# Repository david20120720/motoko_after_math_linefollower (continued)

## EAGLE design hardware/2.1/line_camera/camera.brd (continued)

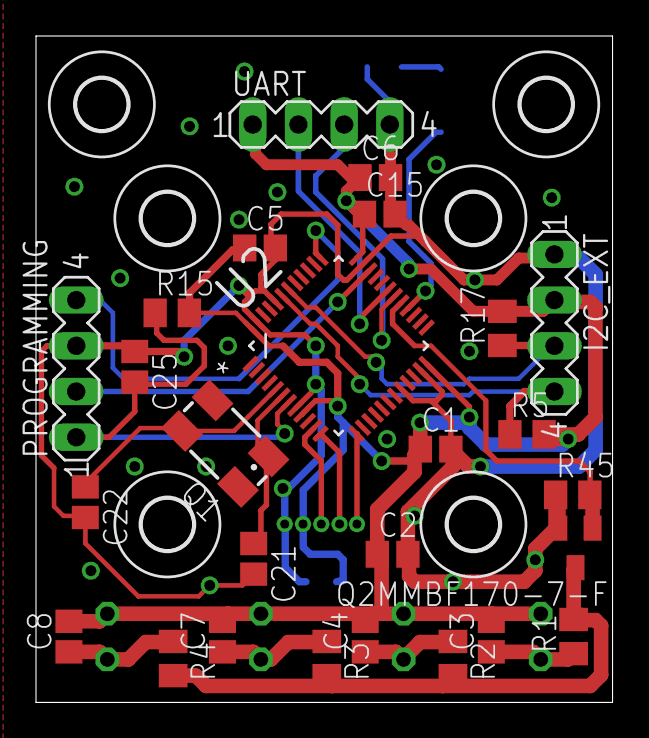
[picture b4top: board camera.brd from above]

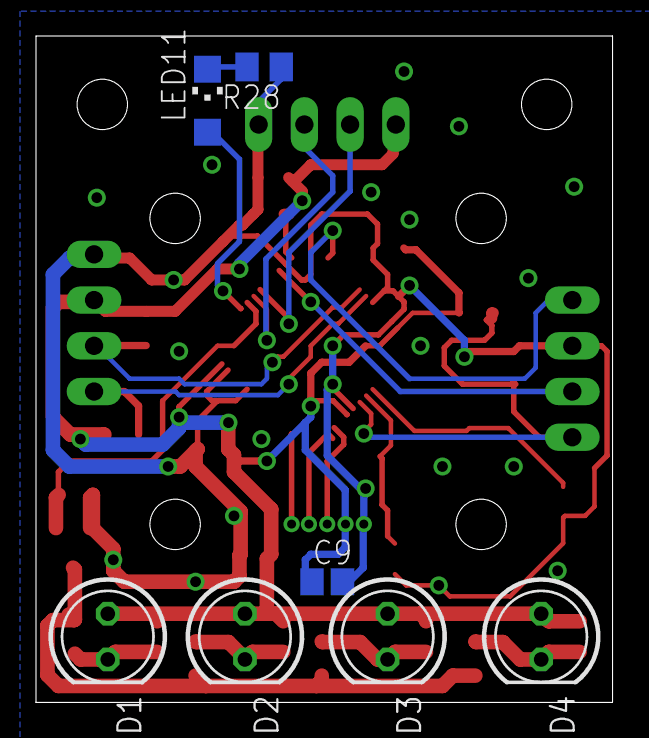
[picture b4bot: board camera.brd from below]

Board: 2 copper layers, 32.0 x 37.0 mm, 39 parts (7 on the bottom side), 19 nets.

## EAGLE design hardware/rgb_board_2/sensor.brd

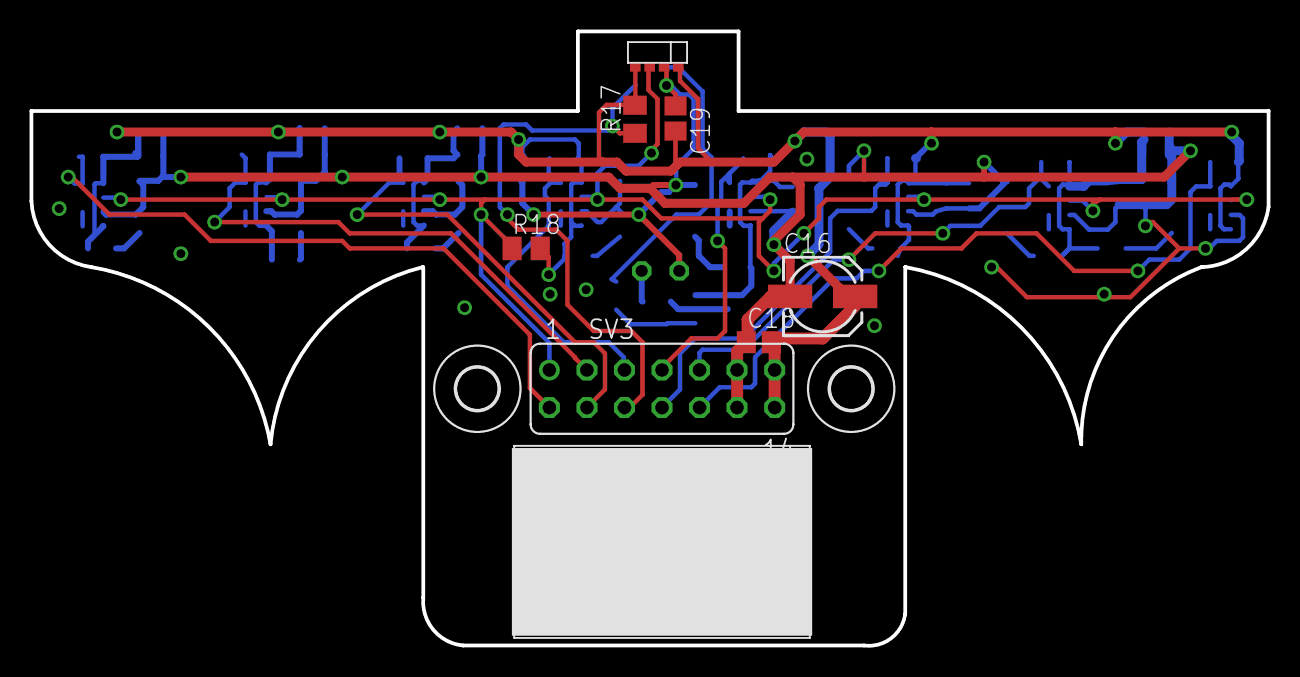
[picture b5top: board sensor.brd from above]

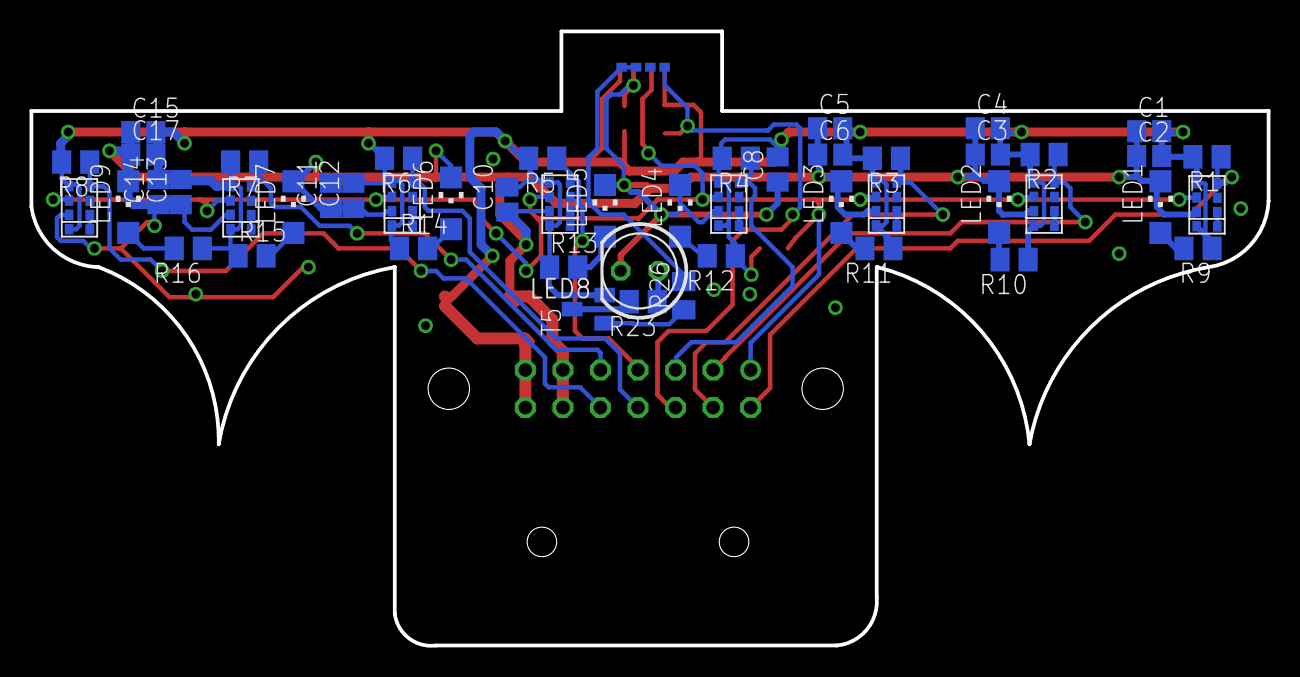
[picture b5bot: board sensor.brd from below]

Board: 2 copper layers, 83.7 x 41.6 mm, 60 parts (50 on the bottom side), 32 nets.

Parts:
C1, C3, C5, C11, C13, C15, C18: 10uF; C0805
C2, C4, C6, C8, C10, C12, C14, C17, C19: 100n; C0805
C16: 22uF; 153CLV-0505
H3, H4: MOUNT-HOLE2.8; 2,8
LED1, LED2, LED3, LED4, LED5, LED6, LED7, LED9: CHIPLED_1206
LED8: LED5MM
R1, R2, R3, R4, R5, R6, R7, R8, R17, R18: 4k7; M0805
R9, R10, R11, R12, R13, R14, R15, R16, R26: 330; M0805
R23: 22; M0805
SV3: FE07-2
T5: SOT23-BEC
U$1, U$4, U$5, U$6, U$7, U$8, U$9, U$10: APDS9950
U$2: APDS9950_EDGE
U$3: BALL_HOLE

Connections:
+3V3: C1.2, C2.2, C3.2, C4.2, C5.2, C6.2, C8.2, C10.2, C11.2, C12.2, C13.2, C14.2, C15.2, C16.+, C17.2, C18.2, C19.2, R1.2, R2.2, R3.2, R4.2, R5.2, R6.2, R7.2, R8.2, R9.1, R10.1, R11.1, R12.1, R13.1, R14.1, R15.1, R16.1, R17.2, R18.2, SV3.13, SV3.14, T5.E, U$1.P$5, U$1.P$8, U$2.P$5, U$2.P$8, U$4.P$5, U$4.P$8, U$5.P$5, U$5.P$8, U$6.P$5, U$6.P$8, U$7.P$5, U$7.P$8, U$8.P$5, U$8.P$8, U$9.P$5, U$9.P$8, U$10.P$5, U$10.P$8
ADC0_: R8.1, SV3.10, U$10.P$1
ADC1_: R7.1, SV3.9, U$9.P$1
ADC2_: R6.1, SV3.8, U$8.P$1
ADC3_: R5.1, SV3.7, U$7.P$1
ADC4_: R4.1, SV3.5, U$6.P$1
ADC5_: R3.1, SV3.4, U$5.P$1
ADC6_: R2.1, SV3.3, U$4.P$1
ADC7_: R1.1, SV3.2, U$1.P$1
ADC8_: R17.1, SV3.6, U$2.P$1
GND: C1.1, C2.1, C3.1, C4.1, C5.1, C6.1, C8.1, C10.1, C11.1, C12.1, C13.1, C14.1, C15.1, C16.-, C17.1, C18.1, C19.1, LED1.C, LED2.C, LED3.C, LED4.C, LED5.C, LED6.C, LED7.C, LED8.K, LED9.C, SV3.11, SV3.12, U$1.P$6, U$2.P$6, U$4.P$6, U$5.P$6, U$6.P$6, U$7.P$6, U$8.P$6, U$9.P$6, U$10.P$6
unnamed: R23.2, T5.C
unnamed: U$4.P$3, U$4.P$4
unnamed: LED1.A, R9.2
unnamed: U$1.P$3, U$1.P$4
unnamed: LED2.A, R10.2
unnamed: LED3.A, R11.2
unnamed: LED4.A, R12.2
unnamed: LED5.A, R13.2
unnamed: U$5.P$3, U$5.P$4
unnamed: LED6.A, R14.2
unnamed: LED7.A, R15.2
unnamed: U$6.P$3, U$6.P$4
unnamed: LED9.A, R16.2
unnamed: R26.2, U$2.P$3, U$2.P$4
unnamed: U$7.P$3, U$7.P$4
unnamed: U$8.P$3, U$8.P$4
unnamed: U$9.P$3, U$9.P$4
unnamed: LED8.A, R23.1
unnamed: U$10.P$3, U$10.P$4
unnamed: R26.1, T5.B
SCL: R18.1, SV3.1, U$1.P$7, U$2.P$7, U$4.P$7, U$5.P$7, U$6.P$7, U$7.P$7, U$8.P$7, U$9.P$7, U$10.P$7

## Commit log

2015-04-26 initial release
2015-05-23 new hardware - camera controlled from main mcu
2015-05-30 common commit
2015-06-02 paper to ossconf added
2015-06-02 oss conf paper
2015-06-04 oss conf paper corrections
2015-08-22 mess cleanded up
2015-12-19 new board
2015-12-20 speed modification
2016-01-15 common
2016-01-18 sources clean up
2016-01-28 camera driver added
2016-02-08 mess clean up
2016-02-11 untold truth added
2016-03-13 sunday commit :)
2016-03-14 untold truth burn up
2016-03-29 camera added
2016-04-09 line sensor
2016-04-16 work on new board
2016-04-27 debug app added
2016-04-30 rewritten into c++
2016-05-05 rewriten into c++
2016-05-12 new hw
2016-06-08 encoders added
2016-06-14 brick
2016-06-23 2.0 version
2016-12-09 board rev 3
